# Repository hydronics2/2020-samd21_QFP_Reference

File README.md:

# samd21_QFP_reference_PCB - based on the Adafruit ItsyBitsy M0

This is a reference design for a SAMD21 for easy SWD programming and testing.  This is a copy of the [Adafruit itsyBitsy m0](https://www.adafruit.com/product/3727)... Using the SAMD21G QFP package among other small part changes. It does not include the memory module for circuit python use. This is similar to the other QFP packages with less memory that I was working with [here](https://github.com/hydronics2/samd21_QFP_reference_PCB).

The QFP package is pretty easy to solder and gives you about the same amount of pins as the original Aruduino 328P.

You can order boards from Oshpark using this link: [project](https://oshpark.com/shared_projects/W1OeQO5j)

Here's a list of parts:
- ATSAMD21G from [digikey](https://www.digikey.com/product-detail/en/microchip-technology/ATSAMD21G18A-AUT/ATSAMD21G18A-AUTCT-ND/4878879).
  -	ARM® Cortex®-M0+ SAM D21G Microcontroller IC 32-Bit 48MHz 256KB (256K x 8) FLASH 48-TQFP (7x7)
- 10 pin SWD Header
  - I included an SMD version [mouser](https://www.mouser.com/ProductDetail/485-752)
  - an even cooler SMD version [mouser](https://www.mouser.com/ProductDetail/485-4048)
  - and a through hole version [mouser](https://www.mouser.com/ProductDetail/200-SHF10501LDTH)
- 3.3V Regulator - generic (18V max input) [mouser](https://www.mouser.com/ProductDetail/511-LDL1117S50R)
- USB micro connector [digikey](https://www.digikey.com/product-detail/en/amphenol-icc-fci/10118194-0001LF/609-4618-1-ND/2785382)
- generic 6mmx6mm tactile button [sparkfun](https://www.sparkfun.com/products/97)
- screw terminal 5mm pitch [sparkfun](https://www.sparkfun.com/products/8432) or [aliexpress](https://www.aliexpress.com/wholesale?catId=0&initiative_id=SB_20190221221755&SearchText=pcb+screw+terminal)

SWD Programmer/Debugger: [Segger](https://www.digikey.com/product-detail/en/segger-microcontroller-systems/8.08.91-J-LINK-EDU-MINI/899-1061-ND/7387472)

## Programming

Adafruit has provided a great [tutorial](https://learn.adafruit.com/how-to-program-samd-bootloaders) for flashing the bootloader onto the board using the segger SWD programmer. It's easier than it looks.

You probably already have the bootloader loader on your computer! Arduino installs them when you install the board files.

# Projects - Pickathon Music Festival

I completed a project at [Pickathon 2019 music festival](https://www.instagram.com/p/B0nMJXHBQjl/) using radio modules and MP3 Players that socketed into a PCB very similar to the reference design above.

Both the sender and receiver boards had radio modules socketed into an SPI header that was exposed via a 8-pin header.

Each receiver board had a mini-MP3 module. When triggered, the MP3 modules output recorded poetry files to small speakers. The MP3 modules worked really well. The 3-watt amplifier sounded pretty good with small speakers in quiet spaces.

## Parts list
- generic Radio module Arduino NRF24L01+ 2.4GHz Wireless RF [amazon](https://www.amazon.com/gp/product/B07GZ17ZWS/ref=ppx_yo_dt_b_asin_title_o01_s00?ie=UTF8&psc=1)
- generic Mini-MP3 module [aliexpress](https://www.aliexpress.com/item/32787304159.html?spm=a2g0s.9042311.0.0.27424c4dwHyDU7)

## Programming

The radio module library is here:
- include <nRF24L01.h>  //https://github.com/nRF24/RF24

The MP3 radio module is here:
- include <DFPlayerMini_Fast.h>  //https://github.com/PowerBroker2/DFPlayerMini_Fast

I slightly modified the DFPlayerMini library so it would work with hardware serial and not software serial as it was originally designed.

The micro-controller communicated with the MP3 player using serial RX/TX.

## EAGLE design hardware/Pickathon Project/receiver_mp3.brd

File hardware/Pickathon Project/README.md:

## Pickathon Hardware

Instead of including a standard SWD programming header, I only exposed the pins at places that would except a custom programming PCB with pogo pins..... so this PCB design (as-is) is probably  not useful to anyone but easy to manipulate.

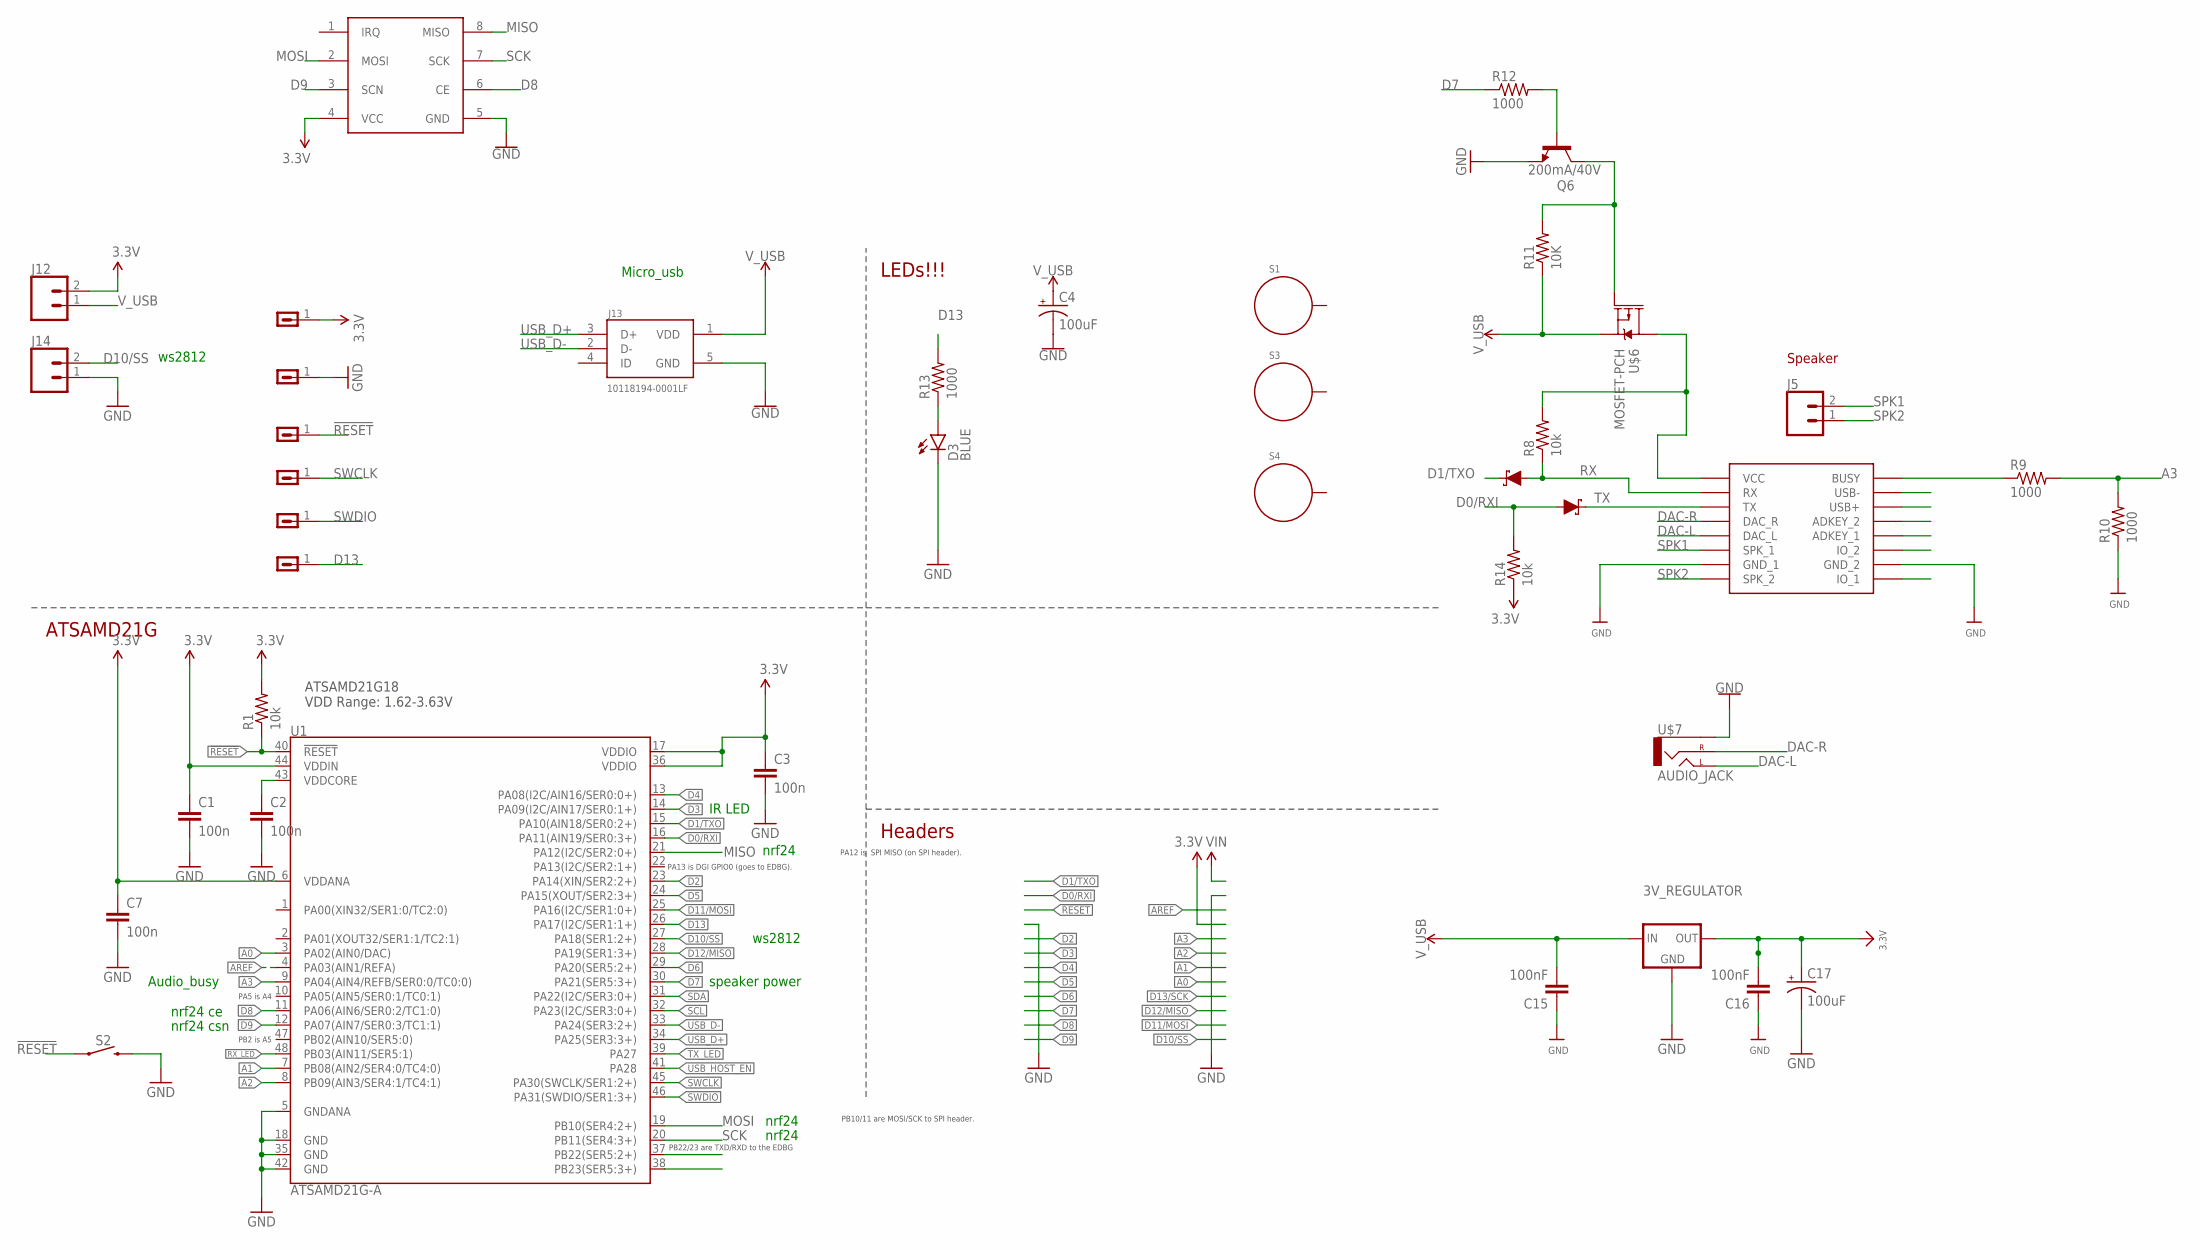
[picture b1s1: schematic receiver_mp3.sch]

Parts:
3V_REGULATOR: LDL1117_5V_REG; SOT223
C1, C2, C3, C7: 100n; 0805
C4, C17: 100uF; CPOL-RADIAL-2.5MM-6.5MM
C15, C16: 100nF; 0805
D1, D5: 3A/40V/500mV; SMA-DIODE
D3: BLUE; LED-1206
J5, J12, J14: CONN_025MM; SCREWTERMINAL-5MM-2
J13: 10118194-0001LF; FRAMATOME_10118194-0001LF
Q6: 200mA/40V; TO-92-EZ
R1, R8, R14: 10k; 0805
R9, R10, R12, R13: 1000; 0805
R11: 10K; 0805
S1, S3, S4: STANDOFF_ELECTRICAL144; STANDOFF_ELECTRICAL_144MILL_NORMAL_SCREW
S2: MOMENTARY-SWITCH-SPST-PTH-6.0MM-KIT; TACTILE_SWITCH_PTH_6.0MM_KIT
U1: ATSAMD21G-A; TQFP-48
U$1: DFPLAYER
U$3: NRF24L01
U$6: MOSFET-PCH; DPAK
U$7: AUDIO_JACK; 1/8"AUDIO_JACK
U$8, U$13, U$18, U$19, U$20, U$22: CONN_011.27MM; 1X01-1.27MM

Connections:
3.3V: 3V_REGULATOR.2 (OUT), 3V_REGULATOR.4 (OUT), C1.1, C3.1, C7.1, C16.2, C17.1 (+), J12.2, R1.2, R14.1, U1.6 (VDDANA), U1.17 (VDDIO), U1.36 (VDDIO), U1.44 (VDDIN), U$3.4 (VCC), U$18.1
!RESET: R1.1, S2.1, U1.40 (!RESET!), U$20.1
A0: U1.3 (PA02(AIN0/DAC))
A1: U1.7 (PB08(AIN2/SER4:0/TC4:0))
A2: U1.8 (PB09(AIN3/SER4:1/TC4:1))
A3: R9.2, R10.2, U1.9 (PA04(AIN4/REFB/SER0:0/TC0:0))
AREF: U1.4 (PA03(AIN1/REFA))
D0/RXI: D5.A, R14.2, U1.16 (PA11(AIN19/SER0:3+))
D1/TXO: D1.C, U1.15 (PA10(AIN18/SER0:2+))
D2: U1.23 (PA14(XIN/SER2:2+))
D3: U1.14 (PA09(I2C/AIN17/SER0:1+))
D4: U1.13 (PA08(I2C/AIN16/SER0:0+))
D5: U1.24 (PA15(XOUT/SER2:3+))
D6: U1.29 (PA20(SER5:2+))
D7: R12.1, U1.30 (PA21(SER5:3+))
D8: U1.11 (PA06(AIN6/SER0:2/TC1:0)), U$3.6 (CE)
D9: U1.12 (PA07(AIN7/SER0:3/TC1:1)), U$3.3 (SCN)
D10/SS: J14.2, U1.27 (PA18(SER1:2+))
D11/MOSI: U1.25 (PA16(I2C/SER1:0+))
D12/MISO: U1.28 (PA19(SER1:3+))
D13: R13.2, U1.26 (PA17(I2C/SER1:1+)), U$8.1
DAC-L: U$1.DAC_L, U$7.LEFT_TIP_1 (LEFT)
DAC-R: U$1.DAC_R, U$7.RIGHT
GND: 3V_REGULATOR.1 (GND), C1.2, C2.2, C3.2, C4.2 (-), C7.2, C15.1, C16.1, C17.2 (-), D3.C, J13.5 (GND), J14.1, Q6.1 (E), R10.1, S2.3 (2), U1.5 (GNDANA), U1.18 (GND), U1.35 (GND), U1.42 (GND), U$1.GND_1, U$1.GND_2, U$3.5 (GND), U$7.GND (SLEEVE), U$13.1
INT1: U1.38 (PB23(SER5:3+))
MISO: U1.21 (PA12(I2C/SER2:0+)), U$3.8 (MISO)
MOSI: U1.19 (PB10(SER4:2+)), U$3.2 (MOSI)
unnamed: R8.2, U$1.VCC, U$6.4 (D)
unnamed: D3.A, R13.1
unnamed: Q6.3 (C), R11.2, U$6.1 (G)
unnamed: Q6.2 (B), R12.2
unnamed: R9.1, U$1.BUSY
RX: D1.A, R8.1, U$1.RX
RX_LED: U1.48 (PB03(AIN11/SER5:1))
SCK: U1.20 (PB11(SER4:3+)), U$3.7 (SCK)
SCL: U1.32 (PA23(I2C/SER3:0+))
SDA: U1.31 (PA22(I2C/SER3:0+))
SPK1: J5.2, U$1.SPK1 (SPK_1)
SPK2: J5.1, U$1.SPK2 (SPK_2)
SWCLK: U1.45 (PA30(SWCLK/SER1:2+)), U$22.1
SWDIO: U1.46 (PA31(SWDIO/SER1:3+)), U$19.1
TX: D5.C, U$1.TX
TX_LED: U1.39 (PA27)
USB_D+: J13.3 (D+), U1.34 (PA25(SER3:3+))
USB_D-: J13.2 (D-), U1.33 (PA24(SER3:2+))
USB_HOST_EN: U1.41 (PA28)
VDDCORE: C2.1, U1.43 (VDDCORE)
V_USB: 3V_REGULATOR.3 (IN), C4.1 (+), C15.2, J12.1, J13.1 (VDD), R11.1, U$6.3 (S)

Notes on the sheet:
PB22/23 are TXD/RXD to the EDBG
PB10/11 are MOSI/SCK to SPI header.
PA12 is SPI MISO (on SPI header).
PA13 is DGI GPIO0 (goes to EDBG).
PA5 is A4
PB2 is A5
LEDs!!!
Headers
ATSAMD21G
ATSAMD21G18 VDD Range: 1.62-3.63V
Micro_usb
IR LED
speaker power
Speaker
Audio_busy
ws2812
nrf24
nrf24 csn
nrf24 ce

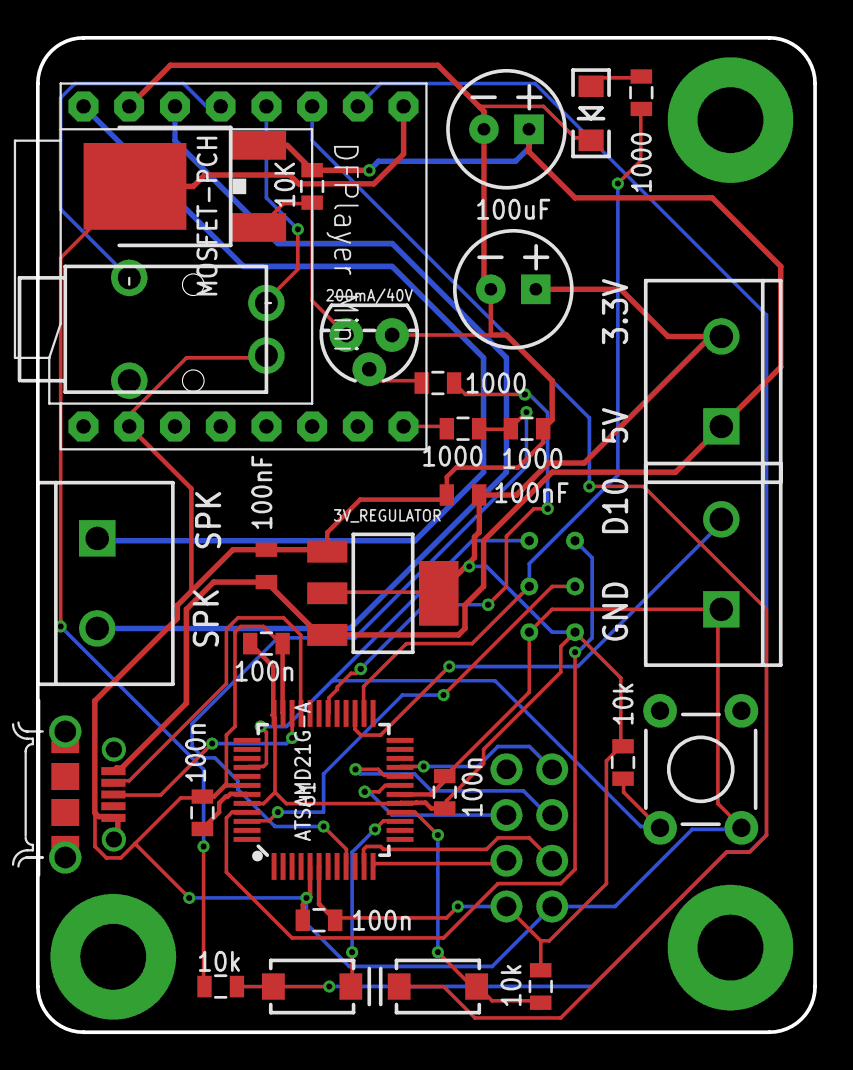
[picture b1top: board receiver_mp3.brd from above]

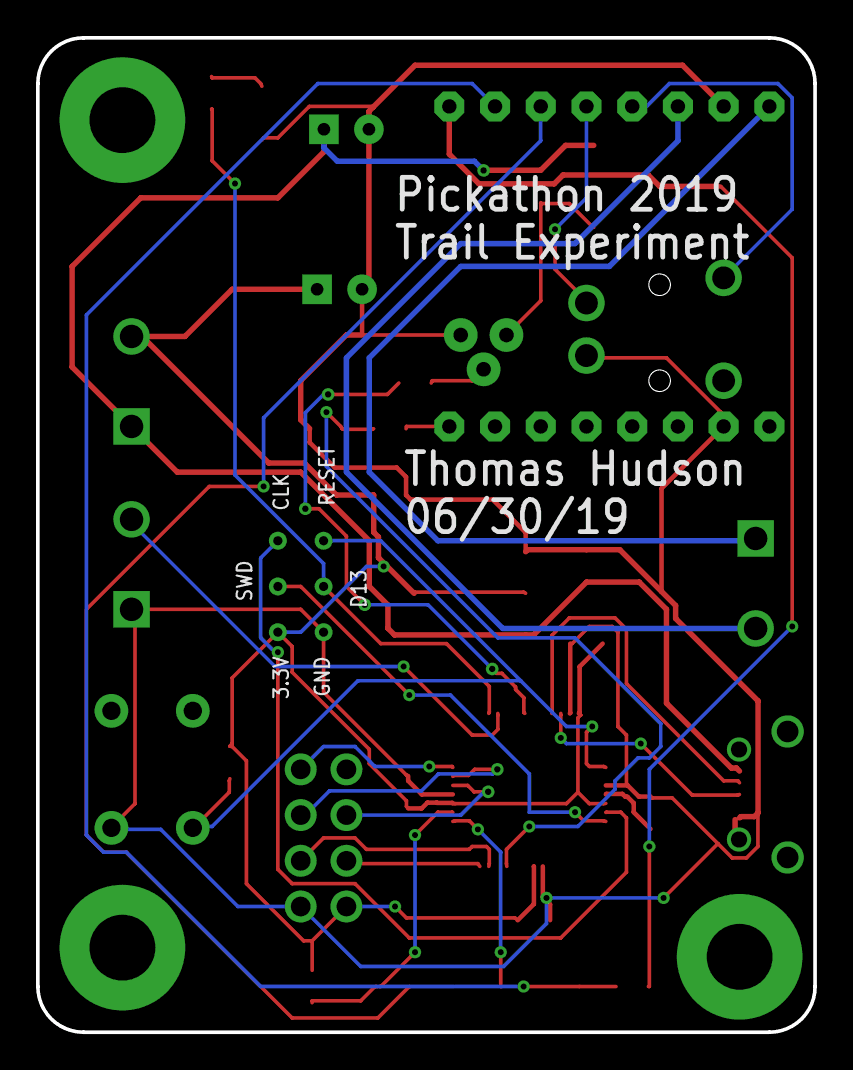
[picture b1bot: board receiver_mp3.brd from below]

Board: 2 copper layers, 43.2 x 55.2 mm, 40 parts (6 on the bottom side), 31 nets.

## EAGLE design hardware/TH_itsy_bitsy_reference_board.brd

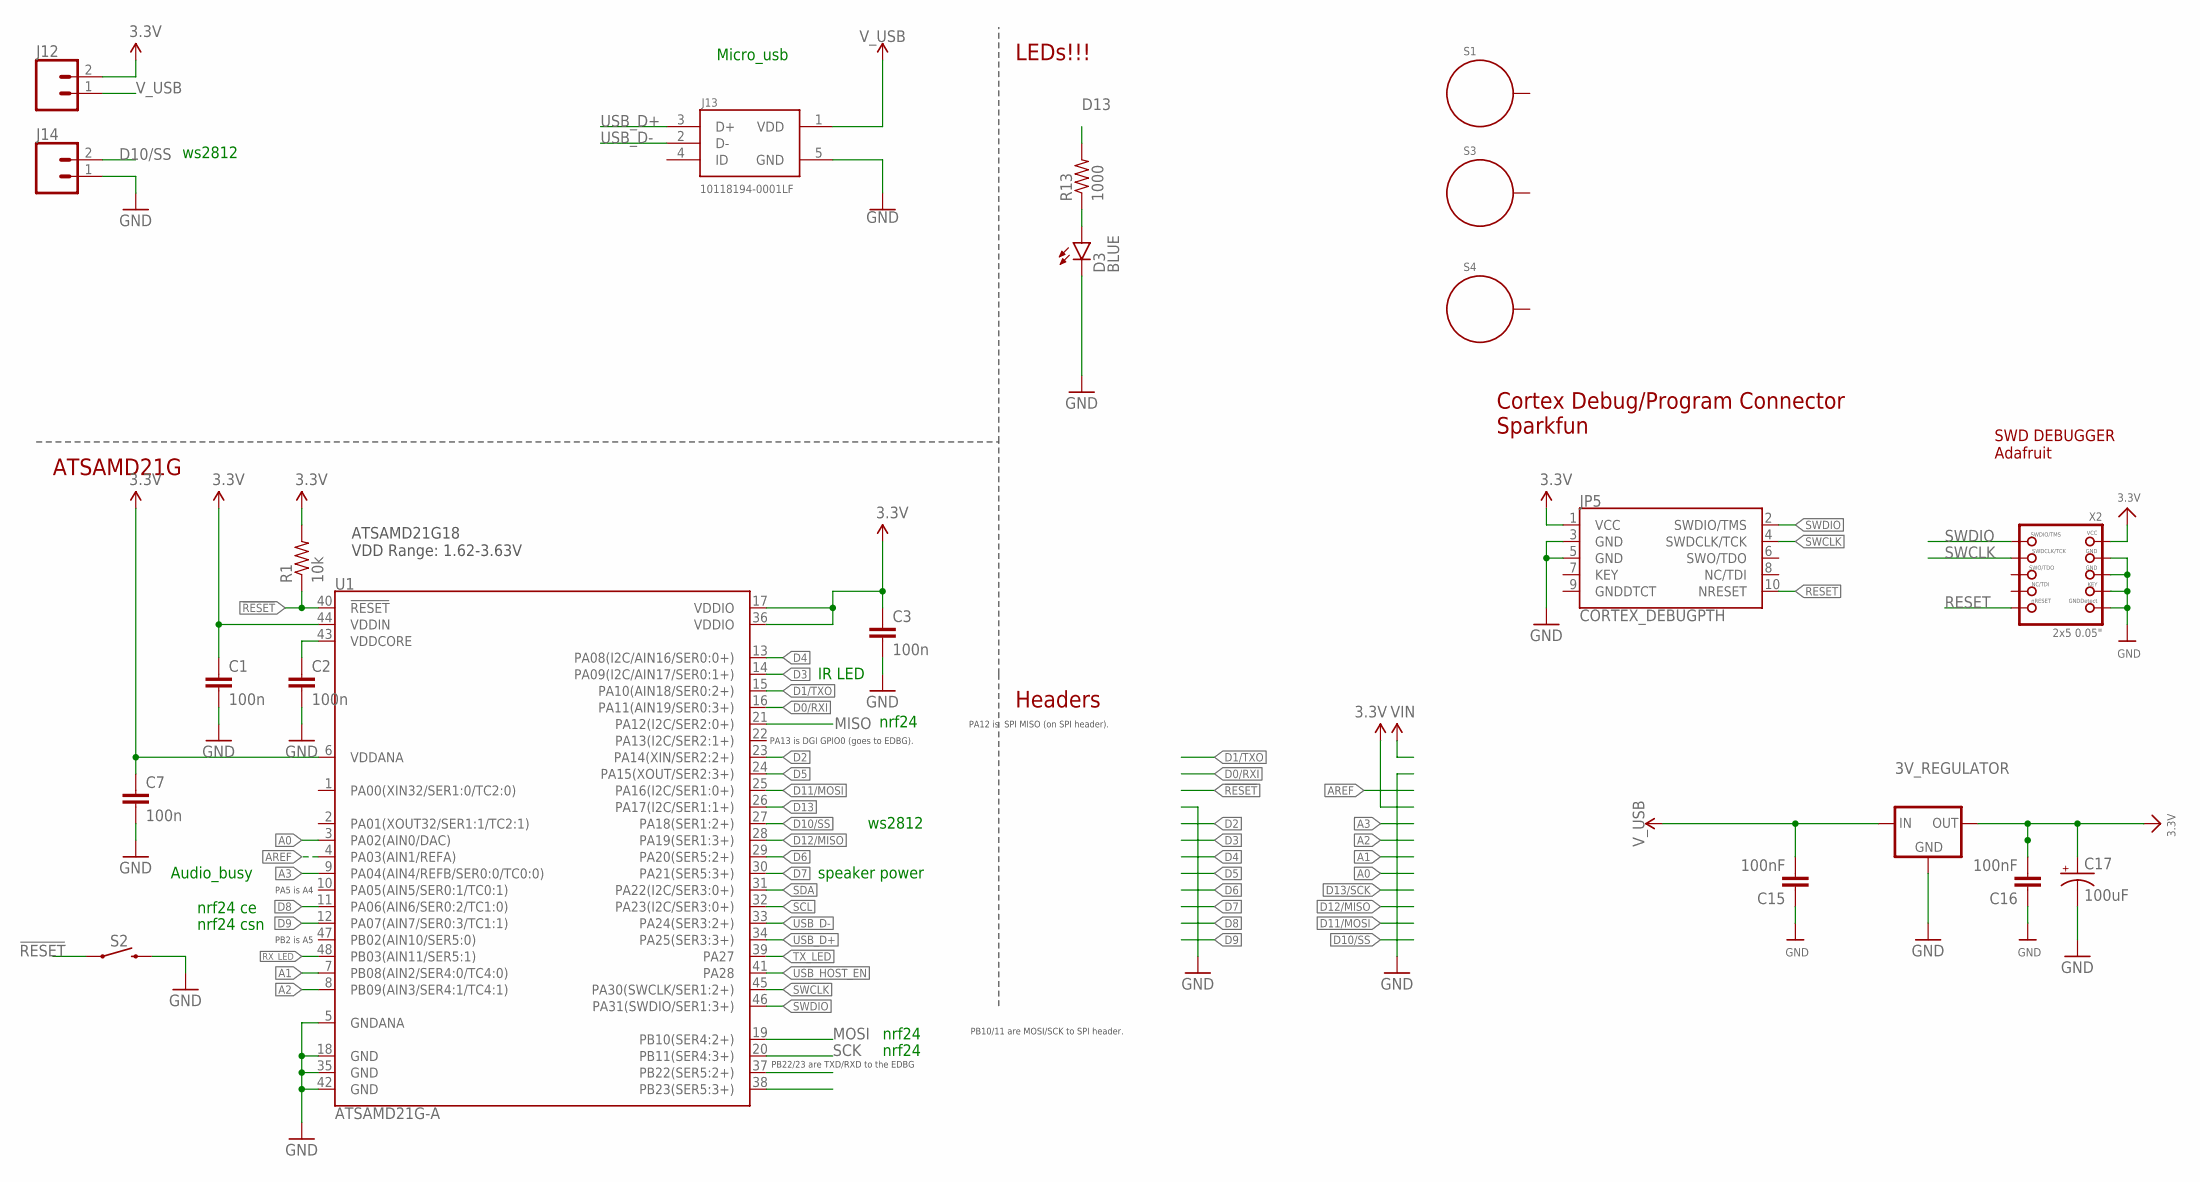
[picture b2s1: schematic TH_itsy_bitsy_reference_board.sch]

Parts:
3V_REGULATOR: LDL1117_5V_REG; SOT223
C1, C2, C3, C7: 100n; 0805
C15, C16: 100nF; 0805
C17: 100uF; CPOL-RADIAL-2.5MM-6.5MM
D3: BLUE; LED-1206
J12, J14: CONN_025MM; SCREWTERMINAL-5MM-2
J13: 10118194-0001LF; FRAMATOME_10118194-0001LF
JP5: CORTEX_DEBUGPTH; 2X5-PTH-1.27MM
R1: 10k; 0805
R13: 1000; 0805
S1, S3, S4: STANDOFF_ELECTRICAL144; STANDOFF_ELECTRICAL_144MILL_NORMAL_SCREW
S2: MOMENTARY-SWITCH-SPST-PTH-6.0MM-KIT; TACTILE_SWITCH_PTH_6.0MM_KIT
U1: ATSAMD21G-A; TQFP-48
X2: 2x5 0.05"; 2X05_1.27MM_BOX_POSTS

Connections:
3.3V: 3V_REGULATOR.2 (OUT), 3V_REGULATOR.4 (OUT), C1.1, C3.1, C7.1, C16.2, C17.1 (+), J12.2, JP5.1 (VCC), R1.2, U1.6 (VDDANA), U1.17 (VDDIO), U1.36 (VDDIO), U1.44 (VDDIN), X2.1 (VCC)
!RESET: R1.1, S2.1, U1.40 (!RESET!)
A0: U1.3 (PA02(AIN0/DAC))
A1: U1.7 (PB08(AIN2/SER4:0/TC4:0))
A2: U1.8 (PB09(AIN3/SER4:1/TC4:1))
A3: U1.9 (PA04(AIN4/REFB/SER0:0/TC0:0))
AREF: U1.4 (PA03(AIN1/REFA))
D0/RXI: U1.16 (PA11(AIN19/SER0:3+))
D1/TXO: U1.15 (PA10(AIN18/SER0:2+))
D2: U1.23 (PA14(XIN/SER2:2+))
D3: U1.14 (PA09(I2C/AIN17/SER0:1+))
D4: U1.13 (PA08(I2C/AIN16/SER0:0+))
D5: U1.24 (PA15(XOUT/SER2:3+))
D6: U1.29 (PA20(SER5:2+))
D7: U1.30 (PA21(SER5:3+))
D8: U1.11 (PA06(AIN6/SER0:2/TC1:0))
D9: U1.12 (PA07(AIN7/SER0:3/TC1:1))
D10/SS: J14.2, U1.27 (PA18(SER1:2+))
D11/MOSI: U1.25 (PA16(I2C/SER1:0+))
D12/MISO: U1.28 (PA19(SER1:3+))
D13: R13.2, U1.26 (PA17(I2C/SER1:1+))
GND: 3V_REGULATOR.1 (GND), C1.2, C2.2, C3.2, C7.2, C15.1, C16.1, C17.2 (-), D3.C, J13.5 (GND), J14.1, JP5.3 (GND), JP5.5 (GND), S2.3 (2), U1.5 (GNDANA), U1.18 (GND), U1.35 (GND), U1.42 (GND), X2.3 (GND), X2.5 (GND), X2.7 (KEY), X2.9 (GNDDETECT)
INT1: U1.38 (PB23(SER5:3+))
MISO: U1.21 (PA12(I2C/SER2:0+))
MOSI: U1.19 (PB10(SER4:2+))
unnamed: D3.A, R13.1
RESET: JP5.10 (NRESET), X2.10 (NRESET)
RX_LED: U1.48 (PB03(AIN11/SER5:1))
SCK: U1.20 (PB11(SER4:3+))
SCL: U1.32 (PA23(I2C/SER3:0+))
SDA: U1.31 (PA22(I2C/SER3:0+))
SWCLK: JP5.4 (SWDCLK/TCK), U1.45 (PA30(SWCLK/SER1:2+)), X2.4 (SWDCLK)
SWDIO: JP5.2 (SWDIO/TMS), U1.46 (PA31(SWDIO/SER1:3+)), X2.2 (SWDIO)
TX_LED: U1.39 (PA27)
USB_D+: J13.3 (D+), U1.34 (PA25(SER3:3+))
USB_D-: J13.2 (D-), U1.33 (PA24(SER3:2+))
USB_HOST_EN: U1.41 (PA28)
VDDCORE: C2.1, U1.43 (VDDCORE)
V_USB: 3V_REGULATOR.3 (IN), C15.2, J12.1, J13.1 (VDD)

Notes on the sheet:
PB22/23 are TXD/RXD to the EDBG
PB10/11 are MOSI/SCK to SPI header.
PA12 is SPI MISO (on SPI header).
PA13 is DGI GPIO0 (goes to EDBG).
PA5 is A4
PB2 is A5
LEDs!!!
Headers
ATSAMD21G
ATSAMD21G18 VDD Range: 1.62-3.63V
Micro_usb
IR LED
speaker power
Audio_busy
ws2812
nrf24
nrf24 csn
nrf24 ce
SWD DEBUGGER Adafruit
Cortex Debug/Program Connector Sparkfun

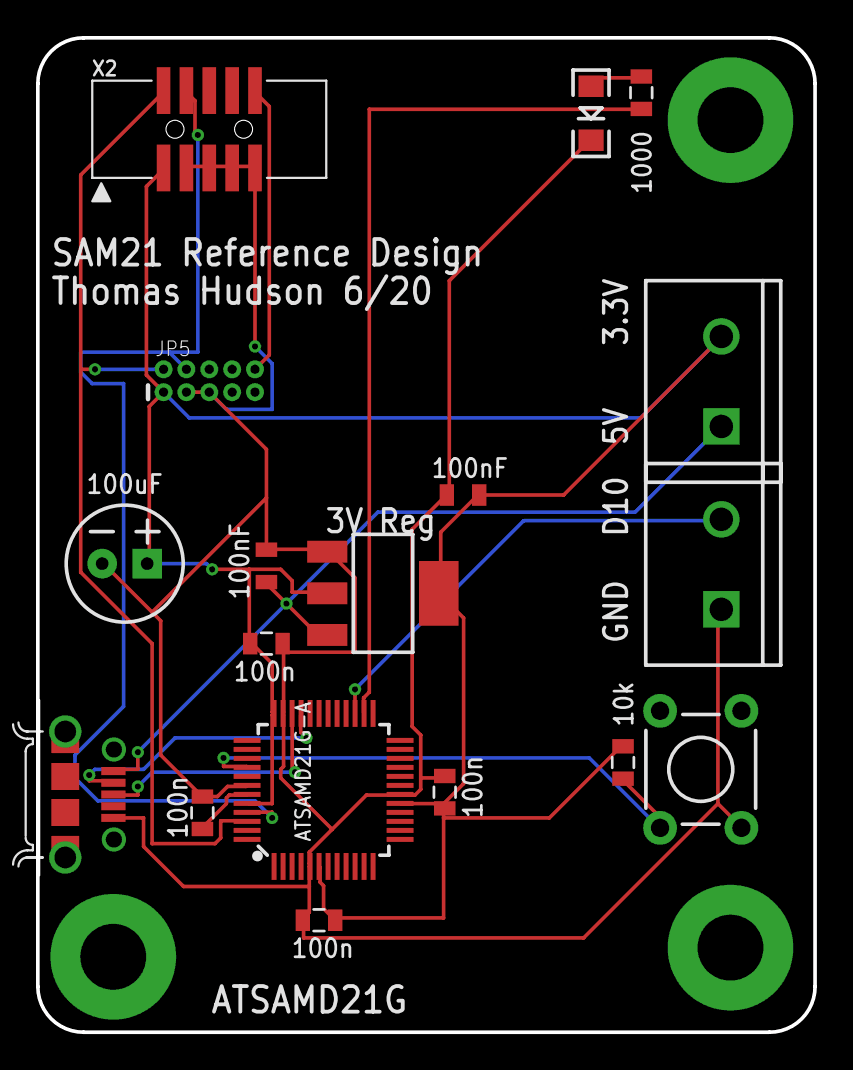
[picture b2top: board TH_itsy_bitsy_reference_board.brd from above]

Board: 2 copper layers, 43.2 x 55.2 mm, 21 parts (0 on the bottom side), 13 nets.

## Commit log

2020-06-03 copy from samd21-qfp
2020-06-03 adjusted to reflect samd21 itsybitsy
2020-06-03 deleted old files
2020-06-03 bootloader
2020-06-03 updated pic
2020-06-03 added pickathon
2020-06-03 added hardware and software for Pickathon

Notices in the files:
parts and their libraries:
SparkFun-Connectors: Licensing: Creative Commons ShareAlike 4.0 International - https://creativecommons.org/licenses/by-sa/4.0
microbuilder: This work is placed in the public domain, and may be freely used for commercial and non-commercial work with the following conditions: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
